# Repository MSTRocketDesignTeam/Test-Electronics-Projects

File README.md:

# Test Electronics
Location of all Test Electronics project files (Created Fall 2025)

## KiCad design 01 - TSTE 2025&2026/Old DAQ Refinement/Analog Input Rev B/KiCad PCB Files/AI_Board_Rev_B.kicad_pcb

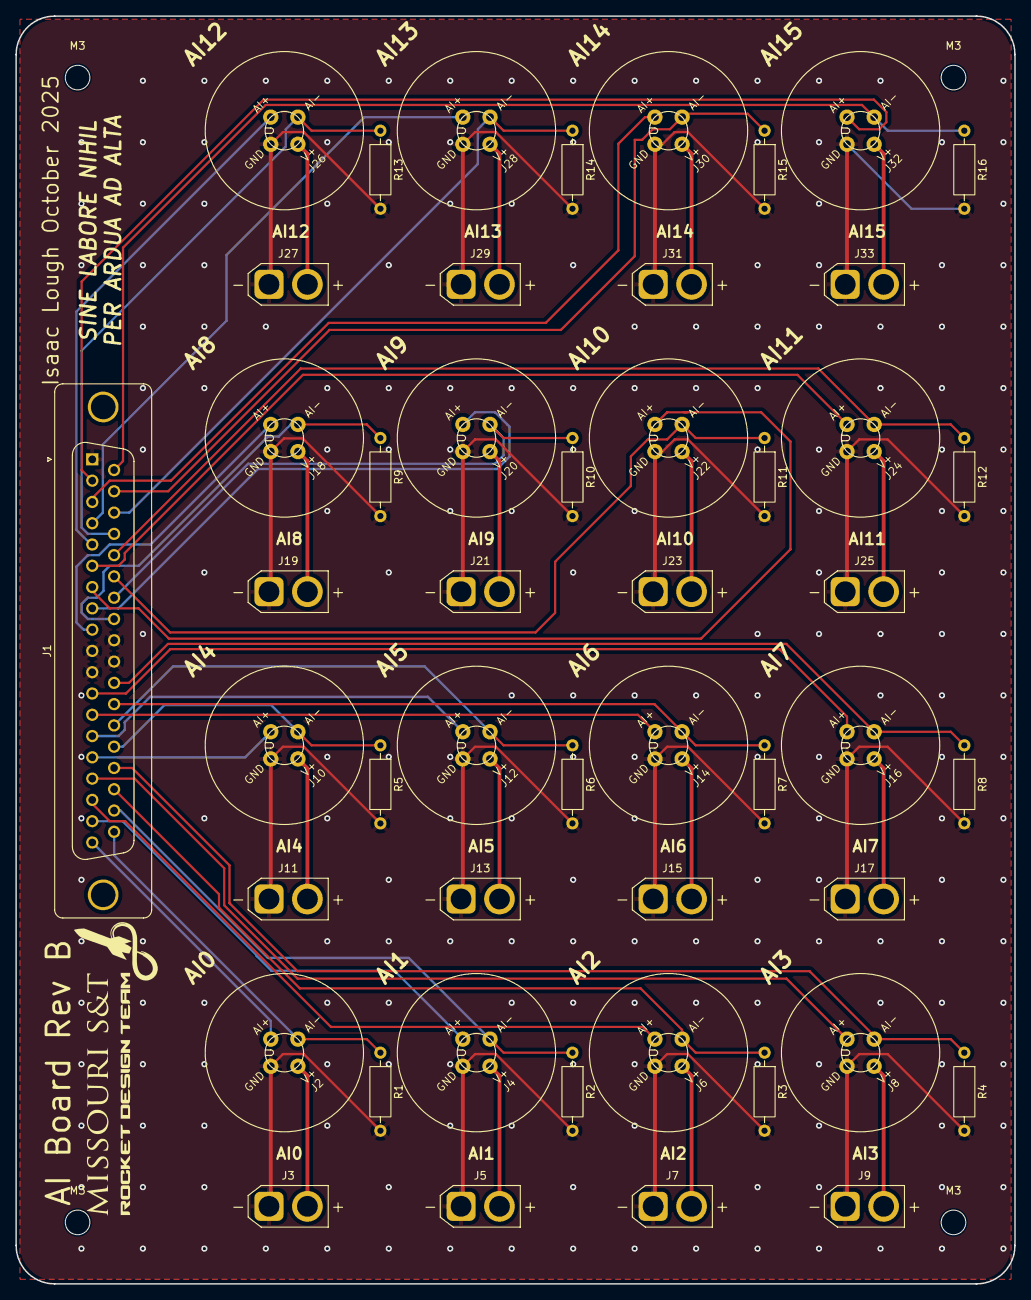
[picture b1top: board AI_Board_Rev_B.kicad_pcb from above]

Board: 2 copper layers, 130.0 x 165.0 mm, 53 parts (0 on the bottom side), 49 nets.

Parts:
J1: DC37_Socket_MountingHoles; DSUB-37_Socket_Vertical_P2.77x2.84mm_MountingHoles
J2: AI0 M12; M12 A-Code Amphenol
J3: AI0 XT30; AMASS_XT30U-F_1x02_P5.0mm_Vertical
J4: AI1 M12; M12 A-Code Amphenol
J5: AI1 XT30; AMASS_XT30U-F_1x02_P5.0mm_Vertical
J6: AI2 M12; M12 A-Code Amphenol
J7: AI2 XT30; AMASS_XT30U-F_1x02_P5.0mm_Vertical
J8: AI3 M12; M12 A-Code Amphenol
J9: AI3 XT30; AMASS_XT30U-F_1x02_P5.0mm_Vertical
J10: AI4 M12; M12 A-Code Amphenol
J11: AI4 XT30; AMASS_XT30U-F_1x02_P5.0mm_Vertical
J12: AI5 M12; M12 A-Code Amphenol
J13: AI5 XT30; AMASS_XT30U-F_1x02_P5.0mm_Vertical
J14: AI6 M12; M12 A-Code Amphenol
J15: AI6 XT30; AMASS_XT30U-F_1x02_P5.0mm_Vertical
J16: AI7 M12; M12 A-Code Amphenol
J17: AI7 XT30; AMASS_XT30U-F_1x02_P5.0mm_Vertical
J18: AI8 M12; M12 A-Code Amphenol
J19: AI8 XT30; AMASS_XT30U-F_1x02_P5.0mm_Vertical
J20: AI9 M12; M12 A-Code Amphenol
J21: AI9 XT30; AMASS_XT30U-F_1x02_P5.0mm_Vertical
J22: AI10 M12; M12 A-Code Amphenol
J23: AI10 XT30; AMASS_XT30U-F_1x02_P5.0mm_Vertical
J24: AI11 M12; M12 A-Code Amphenol
J25: AI11 XT30; AMASS_XT30U-F_1x02_P5.0mm_Vertical
J26: AI12 M12; M12 A-Code Amphenol
J27: AI12 XT30; AMASS_XT30U-F_1x02_P5.0mm_Vertical
J28: AI13 M12; M12 A-Code Amphenol
J29: AI13 XT30; AMASS_XT30U-F_1x02_P5.0mm_Vertical
J30: AI14 M12; M12 A-Code Amphenol
J31: AI14 XT30; AMASS_XT30U-F_1x02_P5.0mm_Vertical
J32: AI15 M12; M12 A-Code Amphenol
J33: AI15 XT30; AMASS_XT30U-F_1x02_P5.0mm_Vertical
M3, M3#2, M3#3, M3#4: MountingHole_3.2mm_M3
R1, R2, R3, R4, R5, R6, R7, R8, R9, R10, R11, R12, R13, R14, R15, R16: 1M; R_Axial_DIN0207_L6.3mm_D2.5mm_P10.16mm_Horizontal

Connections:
/AI0+: J1.19, J2.1
/AI0-: J1.37, J2.2, R1.1
/AI1+: J1.18, J4.1
/AI1-: J1.36, J4.2, R2.1
/AI2+: J1.17, J6.1
/AI2-: J1.35, J6.2, R3.1
/AI3+: J1.16, J8.1
/AI3-: J1.34, J8.2, R4.1
/AI4+: J1.15, J10.1
/AI4-: J1.33, J10.2, R5.1
/AI5+: J1.14, J12.1
/AI5-: J1.32, J12.2, R6.1
/AI6+: J1.13, J14.1
/AI6-: J1.31, J14.2, R7.1
/AI7+: J1.12, J16.1
/AI7-: J1.30, J16.2, R8.1
/AI8+: J1.9, J18.1
/AI8-: J1.27, J18.2, R9.1
/AI9+: J1.8, J20.1
/AI9-: J1.26, J20.2, R10.1
/AI10+: J1.7, J22.1
/AI10-: J1.25, J22.2, R11.1
/AI11+: J1.6, J24.1
/AI11-: J1.24, J24.2, R12.1
/AI12+: J1.5, J26.1
/AI12-: J1.23, J26.2, R13.1
/AI13+: J1.4, J28.1
/AI13-: J1.22, J28.2, R14.1
/AI14+: J1.3, J30.1
/AI14-: J1.21, J30.2, R15.1
/AI15+: J1.2, J32.1
/AI15-: J1.20, J32.2, R16.1
GND: J1.1, J1.10, J1.11, J1.28, J1.29, J2.4, J3.1, J4.4, J5.1, J6.4, J7.1, J8.4, J9.1, J10.4, J11.1, J12.4, J13.1, J14.4, J15.1, J16.4, J17.1, J18.4, J19.1, J20.4, J21.1, J22.4, J23.1, J24.4, J25.1, J26.4, J27.1, J28.4, J29.1, J30.4, J31.1, J32.4, J33.1, R1.2, R2.2, R3.2, R4.2, R5.2, R6.2, R7.2, R8.2, R9.2, R10.2, R11.2, R12.2, R13.2, R14.2, R15.2, R16.2
unnamed: J2.3, J3.2
unnamed: J4.3, J5.2
unnamed: J6.3, J7.2
unnamed: J8.3, J9.2
unnamed: J10.3, J11.2
unnamed: J12.3, J13.2
unnamed: J14.3, J15.2
unnamed: J16.3, J17.2
unnamed: J18.3, J19.2
unnamed: J20.3, J21.2
unnamed: J22.3, J23.2
unnamed: J24.3, J25.2
unnamed: J26.3, J27.2
unnamed: J28.3, J29.2
unnamed: J30.3, J31.2
unnamed: J32.3, J33.2

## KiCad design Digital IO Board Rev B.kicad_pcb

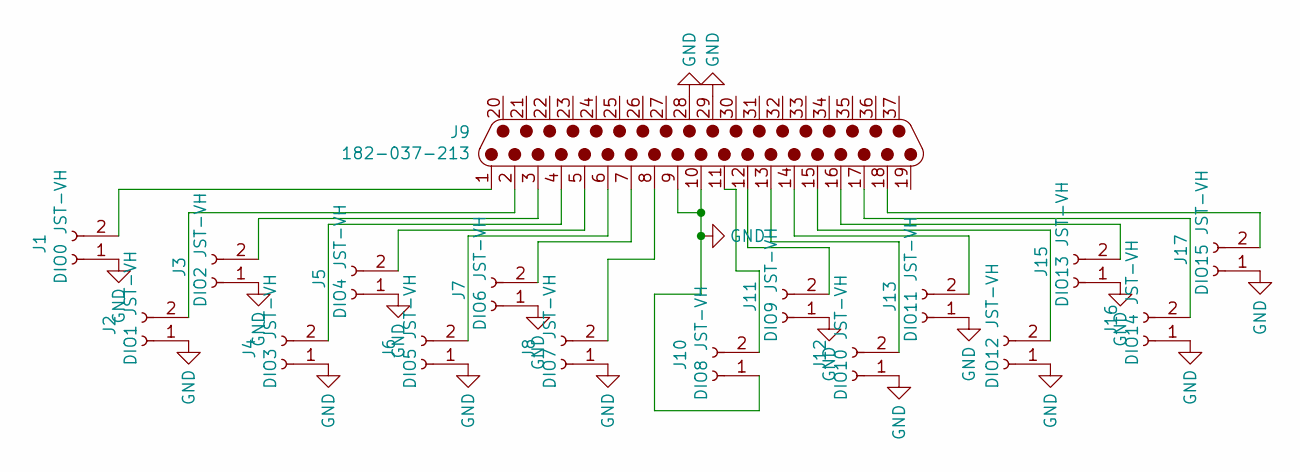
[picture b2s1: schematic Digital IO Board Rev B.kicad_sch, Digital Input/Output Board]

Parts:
J1: DIO0 JST-VH; JST_VH_B2P-VH-B_1x02_P3.96mm_Vertical
J2: DIO1 JST-VH; JST_VH_B2P-VH-B_1x02_P3.96mm_Vertical
J3: DIO2 JST-VH; JST_VH_B2P-VH-B_1x02_P3.96mm_Vertical
J4: DIO3 JST-VH; JST_VH_B2P-VH-B_1x02_P3.96mm_Vertical
J5: DIO4 JST-VH; JST_VH_B2P-VH-B_1x02_P3.96mm_Vertical
J6: DIO5 JST-VH; JST_VH_B2P-VH-B_1x02_P3.96mm_Vertical
J7: DIO6 JST-VH; JST_VH_B2P-VH-B_1x02_P3.96mm_Vertical
J8: DIO7 JST-VH; JST_VH_B2P-VH-B_1x02_P3.96mm_Vertical
J9: 182-037-213; DSUB-37_Socket_Vertical_P2.77x2.84mm_MountingHoles
J10: DIO8 JST-VH; JST_VH_B2P-VH-B_1x02_P3.96mm_Vertical
J11: DIO9 JST-VH; JST_VH_B2P-VH-B_1x02_P3.96mm_Vertical
J12: DIO10 JST-VH; JST_VH_B2P-VH-B_1x02_P3.96mm_Vertical
J13: DIO11 JST-VH; JST_VH_B2P-VH-B_1x02_P3.96mm_Vertical
J14: DIO12 JST-VH; JST_VH_B2P-VH-B_1x02_P3.96mm_Vertical
J15: DIO13 JST-VH; JST_VH_B2P-VH-B_1x02_P3.96mm_Vertical
J16: DIO14 JST-VH; JST_VH_B2P-VH-B_1x02_P3.96mm_Vertical
J17: DIO15 JST-VH; JST_VH_B2P-VH-B_1x02_P3.96mm_Vertical

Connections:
GND: J1.1, J2.1, J3.1, J4.1, J5.1, J6.1, J7.1, J8.1, J9.9, J9.10, J9.28, J9.29, J10.1, J11.1, J12.1, J13.1, J14.1, J15.1, J16.1, J17.1
unnamed: J1.2, J9.1
unnamed: J2.2, J9.2
unnamed: J3.2, J9.3
unnamed: J4.2, J9.4
unnamed: J5.2, J9.5
unnamed: J6.2, J9.6
unnamed: J7.2, J9.7
unnamed: J8.2, J9.8
unnamed: J9.11, J10.2
unnamed: J9.12, J11.2
unnamed: J9.13, J12.2
unnamed: J9.14, J13.2
unnamed: J9.15, J14.2
unnamed: J9.16, J15.2
unnamed: J9.17, J16.2
unnamed: J9.18, J17.2

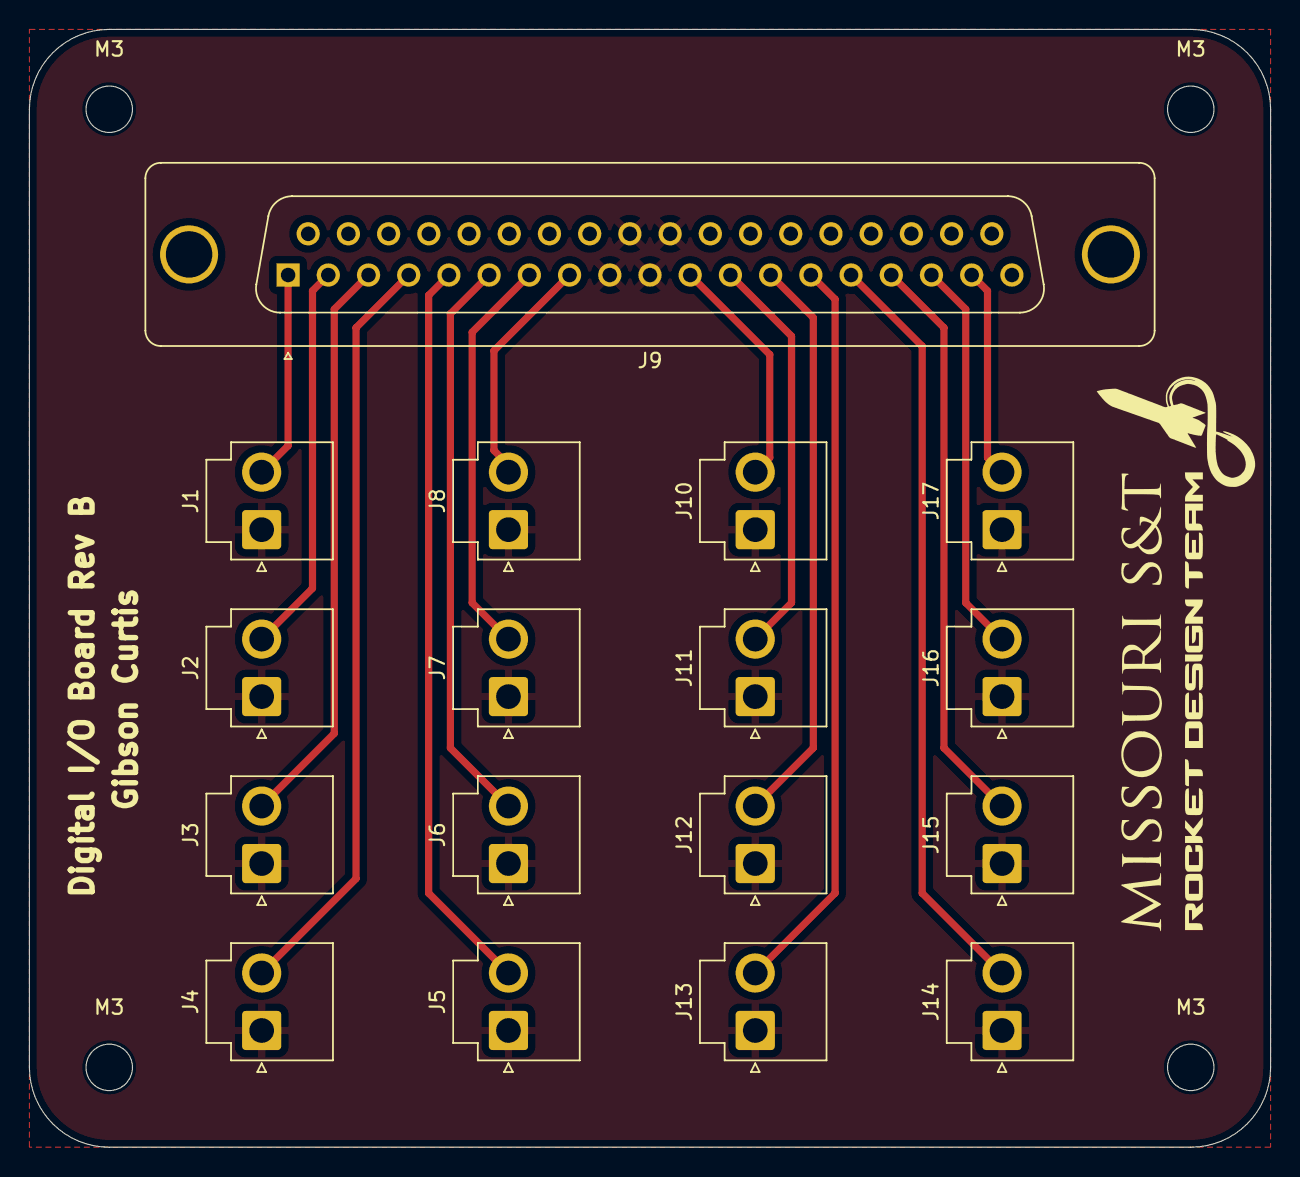
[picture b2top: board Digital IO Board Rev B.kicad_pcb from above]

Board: 2 copper layers, 85.5 x 77.0 mm, 21 parts (0 on the bottom side), 17 nets.

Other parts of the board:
M3, M3#2, M3#3, M3#4: MountingHole_3.2mm_M3

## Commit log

2025-10-09 README.md
2025-10-09 Hub for old projects
2025-10-09 Hub for 2025-2026 projects
2025-10-09 Changes to the old DAQ system
2025-10-09 Digital IO Rev B
2025-10-09 Relocating
2025-10-09 placeholder
2025-10-09 rid placeholder
2025-10-09 rid improper
2025-10-12 Deleting Old Stuff
2025-10-14 Commiting AI Board Edits
2025-10-18 Final Files
2025-10-19 Vias Change Upload
2025-11-06 Create placeholder
2025-11-11 Sending in Blake's schems
2025-11-11 Deleting Placeholder
2025-11-11 Pushing Tyler's schem
2025-11-17 Pushing Mux80 Schem
